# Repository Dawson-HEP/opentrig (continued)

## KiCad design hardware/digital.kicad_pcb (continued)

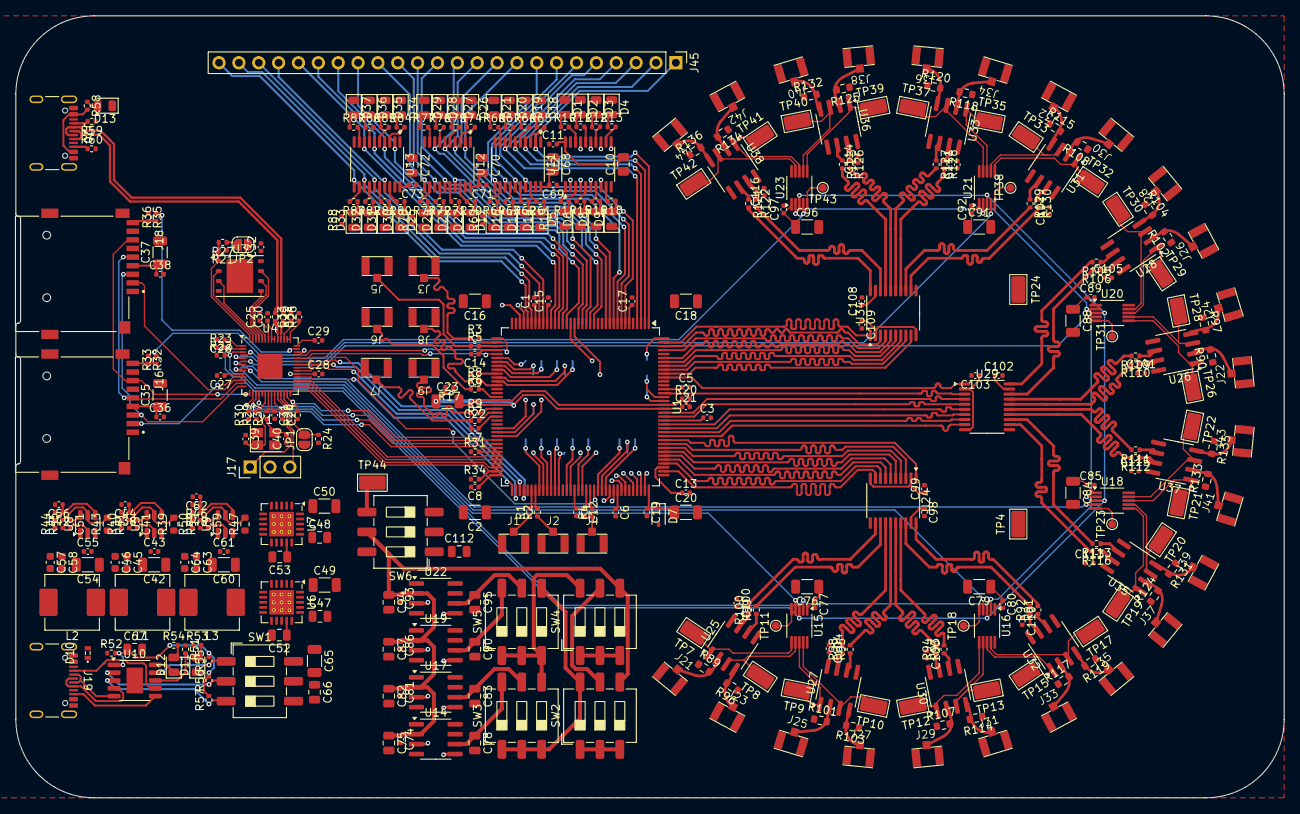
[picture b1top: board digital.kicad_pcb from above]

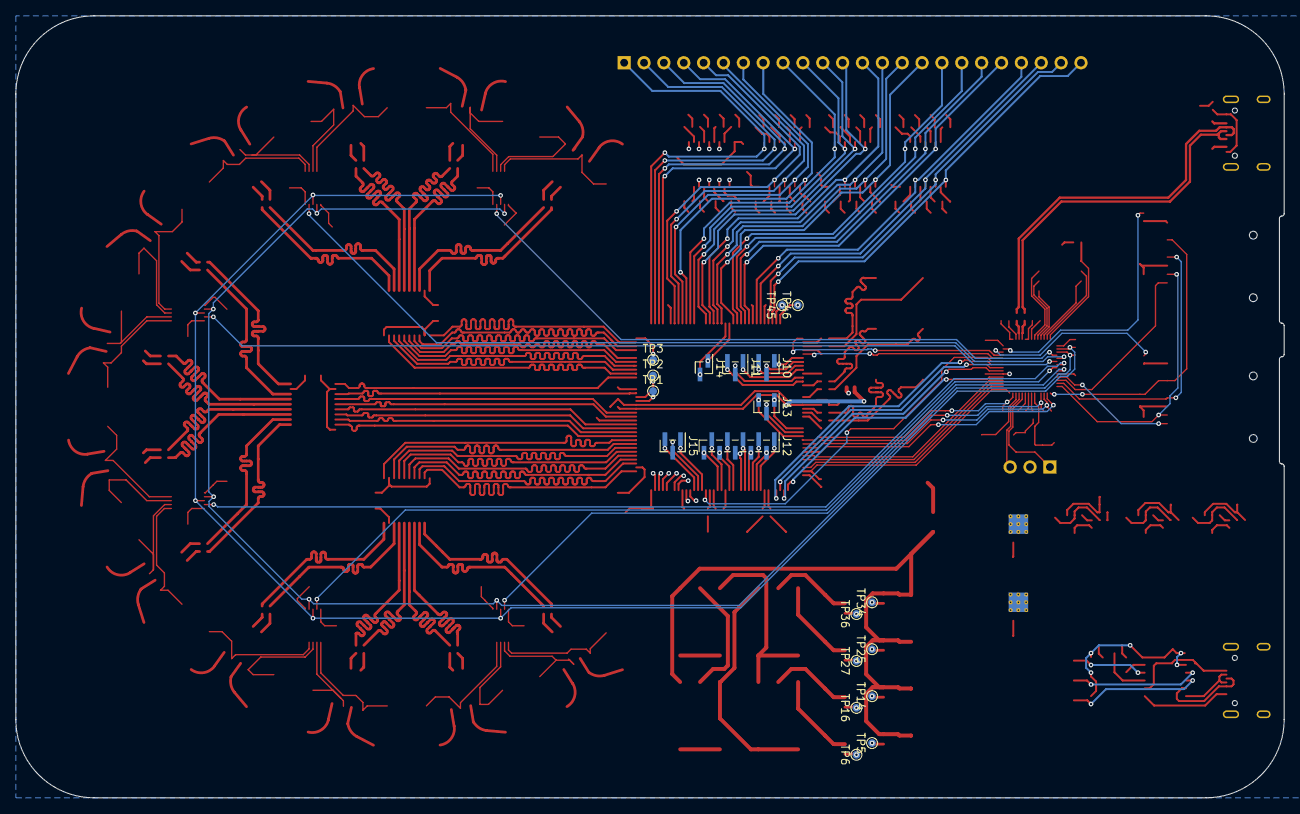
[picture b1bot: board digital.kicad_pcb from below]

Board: 4 copper layers, 162.2 x 100.0 mm, 429 parts (19 on the bottom side), 382 nets.

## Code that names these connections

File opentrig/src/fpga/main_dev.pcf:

set_io mcu_clk 37       # GPIO27
#set_io ext_clk 38               # External clock
        set_io ext_clk 44        # Internal clock from SIM PICO

set_io pll_clk 39
set_io pll_lock 41      # GPIO26

set_io t_zero_received 73

set_io spi_clk 70
set_io spi_cs 71
set_io spi_si 68
set_io spi_so 67

set_io veto_in 52
set_io trig_in 49
set_io trig_id 93
        #set_io veto_in 21
        #set_io trig_in 20
        #set_io trig_id 42

set_io trig_out 55
set_io veto_out 56

set_io global_reset 94
set_io mem_swap_interrupt 64


# mcu connections

set_io interrupt 63
set_io reset 64

# inputs
set_io c_input[0] 1
set_io c_input[1] 2
set_io c_input[2] 3
set_io c_input[3] 4
set_io c_input[4] 7
set_io c_input[5] 8
set_io c_input[6] 9
set_io c_input[7] 10
set_io c_input[8] 11
set_io c_input[9] 12
set_io c_input[10] 15
set_io c_input[11] 16
set_io c_input[12] 17
set_io c_input[13] 18
set_io c_input[14] 19
set_io c_input[15] 22
set_io c_input[16] 23
set_io c_input[17] 24
set_io c_input[18] 25
set_io c_input[19] 26
set_io c_input[20] 28
set_io c_input[21] 29
set_io c_input[22] 31
set_io c_input[23] 32

# led
set_io led[0] 98
set_io led[1] 99
set_io led[2] 101
set_io led[3] 102
set_io led[4] 104
set_io led[5] 105
set_io led[6] 106
set_io led[7] 107


# debug outputs
set_io aux_out[0] 80
set_io aux_out[1] 81
set_io aux_out[2] 82
set_io aux_out[3] 83
set_io aux_out[4] 84
set_io aux_out[5] 85
set_io aux_out[6] 87
set_io aux_out[7] 88
set_io aux_out[8] 90
set_io aux_out[9] 91

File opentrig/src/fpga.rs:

use defmt::*;
use embassy_rp::{
    gpio::{AnyPin, Input, Level, Output, Pull},
    pwm::{Config as PWMConfig, Pwm, SetDutyCycle},
    spi::{Async, Config as SPIConfig, Instance, Phase, Polarity, Spi},
};
use embassy_time::Timer;

pub struct DAQFpga<'a, T>
where
    T: Instance,
{
    spi: Spi<'a, T, Async>,

    cs: Output<'a>,
    creset: Output<'a>,
    cdone: Input<'a>,

    mcu_clk: Pwm<'a>,
    pll_lock: Input<'a>,

    reset_pin: Output<'a>,
    interrupt: Input<'a>,

    read_buffer: [u8; 16],
}

pub fn daq_fpga_spi_config() -> SPIConfig {
    let mut config = SPIConfig::default();
    config.frequency = 5_000_000;
    config.polarity = Polarity::IdleHigh;
    config.phase = Phase::CaptureOnSecondTransition;
    config
}

pub fn daq_fpga_clock_config() -> PWMConfig {
    let clock_freq_hz = embassy_rp::clocks::clk_sys_freq();
    let divider = 1u8;
    let period = (clock_freq_hz / (10_000_000 * divider as u32)) as u16 - 1;

    let mut c = PWMConfig::default();
    c.top = period;
    c.divider = divider.into();

    c
}

impl<'a, T> DAQFpga<'a, T>
where
    T: Instance,
{
    pub fn new(
        spi_bus: Spi<'a, T, Async>,

        cs: AnyPin,
        creset: AnyPin,
        cdone: AnyPin,

        mcu_clk: Pwm<'a>,
        pll_lock: AnyPin,

        reset_pin: AnyPin,
        interrupt: AnyPin,
    ) -> Self {
        Self {
            spi: spi_bus,

            cs: Output::new(cs, Level::Low),
            creset: Output::new(creset, Level::Low),
            cdone: Input::new(cdone, Pull::None),

            mcu_clk: mcu_clk,
            pll_lock: Input::new(pll_lock, Pull::Down),

            reset_pin: Output::new(reset_pin, Level::High),
            interrupt: Input::new(interrupt, Pull::None),

            read_buffer: [0u8; 16],
        }
    }

    pub async fn configure(&mut self, bitstream: &'static [u8]) -> Result<(), ()> {
        if self.cdone.is_low() {
            info!("config proceed");
        } else {
            info!("config err, cdone already high");
            return Err(());
        }

        self.creset.set_high();
        Timer::after_micros(1200).await;

        self.cs.set_high();
        self.spi.write(&[0]).await.map_err(|_| ())?;
        info!("ok 8 dummy");
        self.cs.set_low();

        info!("bitstream size: {}", bitstream.len());
        self.spi.write(bitstream).await.map_err(|_| ())?;
        info!("ok bitstream");
        self.cs.set_high();

        if self.cdone.is_high() {
            info!("last 49(56) cycles");
            self.spi.write(&[0xFFu8; 7]).await.map_err(|_| ())?;
            info!("last config 56 bits ok");
            info!("confirm config done");
        } else {
            warn!("cdone never high");
            return Err(());
        }

        Ok(())
    }

    pub async fn setup_clocks(&mut self) -> Result<(), ()> {
        self.mcu_clk.set_duty_cycle_percent(50).map_err(|_| ())?;

        while self.pll_lock.is_low() {
            warn!("pll not locked");
            Timer::after_millis(500).await;
        }
        info!("pll locked");

        Ok(())
    }

    pub fn reset(&mut self) -> Result<(), ()> {
        self.reset_pin.set_low();
        self.reset_pin.set_high();

        match self.interrupt.is_low() {
            true => {
                info!("reset success");
                Ok(())
            }
            false => {
                warn!("reset failed");
                Err(())
            }
        }
    }

    pub async fn await_sample(&mut self) {
        self.interrupt.wait_for_falling_edge().await;
    }

    pub fn last_sample_bytes(& self) -> &[u8; 16] {
        &self.read_buffer
    }

    // pub fn read_sample(&mut self) -> Result<DAQSample, ()> {
    pub fn read_sample(&mut self) {
        self.cs.set_low();
        self.spi
            .blocking_read(&mut self.read_buffer)
            .map_err(|_| ()).unwrap();
        self.cs.set_high();
    }
}

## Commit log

2025-06-30 Added the DAC/ADC array for analog conversion.
    Added an array of 6 quad-channels DAC with I2C interface to control the threshold voltage of a set of 12 dual channel ADCs. Loose, general wiring of FPGA and MCU present, detailed schematics in the w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
2025-07-02 Added SD card readers and USB-C for power in.
2025-07-03 generate pdfs
2025-07-09 Small aesthetic changes and small rework of power sheet.
2025-07-09 add power redundancy with OR-ing controller
2025-07-10 complete power
2025-07-11 reroute dac + comparators
2025-07-11 series resistors
2025-07-11 cleanup
2025-07-11 rewire
2025-07-11 annotate dip switches
2025-07-12 add notice
2025-07-12 cleanup kicad files
2025-07-12 refactor
2025-07-12 kicad + Rust exclusions
2025-07-12 Rust embassy boilerplate
2025-07-15 fpga .gitignore
2025-07-16 complete schematic wiring
2025-07-16 add kicad files
2025-07-16 add schematic pdf
2025-07-16 basic verilog bitstream programming
2025-07-17 remove kicad autosaves
2025-07-17 update power system + add LCSC part numbers
2025-07-17 apply manufacturing BOM
2025-07-18 route digital inputs
2025-07-18 route power
2025-07-18 route more
2025-07-18 route mcu
2025-07-19 wire until sipm power
2025-07-20 route
2025-07-20 route all signal
2025-07-20 add board edge
2025-07-20 finish routing
2025-07-20 add edges
2025-07-21 finish pcb
2025-07-21 drc check pass
2025-07-21 fabrication
2025-07-31 not working
2025-08-02 fix bitstream writing
2025-08-02 fix fpga synth target
2025-08-02 rudimentary communication
2025-08-02 add trig id pin
2025-08-03 basic testing suite
2025-08-03 working shifting out
2025-08-03 trigger id generation
2025-08-03 event pins encoding
2025-08-04 working input clk pll
2025-08-04 shift in trigger_id
2025-08-05 update to newer embassy
2025-08-05 read over trigger id
2025-08-05 cleanup trigger
2025-08-05 read clock counter
2025-08-05 trigger time
2025-08-05 reduce clock bit width to 48
2025-08-05 registering inputs
2025-08-05 remove data
2025-08-05 working veto
2025-08-05 veto simulation
2025-08-05 event management
2025-08-05 refactor fpga code
2025-08-07 dac writing
2025-08-07 tester
2025-08-07 remove dac
2025-08-08 internal trigger bit
2025-08-11 add watchdog + success in physical reading
2025-08-11 add trigger data
2025-08-14 Initial DacManager implementation (WARNING!) This module is NOT YET TESTED. Expect future changes and refrain from immediate usage if possible. Future functionality: Change vref mode, Change gain mod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
2025-08-19 Added write functions for all MCP registers.
2025-08-28 branch for_cli, hopefully. initial daqsample serialisation test
2025-08-29 incompatible differences between opentrig and usb_raw_bulk
2025-09-02 working version of multicore with usb_raw_bulk
2025-09-05 Complete MCP4728 manager for the DAQ.
2025-09-05 ~half of function inputs are made, with u8 documentation. beginning to connect inputs with core transfers properly
2025-09-06 functions calling from the CLI inputs completed
2025-09-08 inputs work fully properly and with info! messages for working or not working. inclusion of daq causes program to crash for some reason.
2025-09-08 working without daq
2025-09-08 added rusb_for_tests
2025-09-08 working with new DacManager stuff
2025-09-08 Cli code with command encoding. Needs to be reviewed and tested
2025-09-08 Fixed zip removing trailing arguments
2025-09-08 Fixed a bug introduced when taking excess args
2025-09-09 Added more thorough error mapping.
2025-09-09 Added info calls for easier debugging and control.
2025-09-09 all function inputs work with .await.unwrap()
2025-09-09 fix watchdog
2025-09-10 python cli
2025-09-10 opentrig
2025-09-10 rusb cli
2025-09-10 Last fix.
2025-09-14 Added rust CLI initial commit
2025-09-14 Added basic serial, readings packets from DAQ (to test)
2025-09-15 tons of stuff done
2025-09-15 Test
2025-09-15 Made readout work
2025-09-15 Added serial
2025-09-15 working version on pico! (only if computer/usb-connection is active, for the moment)
2025-09-15 Added no_serial_cli to git
2025-09-15 andy's location.py
2025-09-15 new main test
2025-09-15 main.bin for fpga
2025-09-15 remove old
2025-09-15 new cli
2025-09-16 change pcf for DESY
2025-09-16 encoding directly from fpga sent over should work
2025-09-16 simplify CLI buffering transfer
2025-09-16 Added MCP manager.
2025-09-16 Correct end and start byte
2025-09-16 chec end bit
2025-09-16 unworking minimal cli
2025-09-16 Added count events
2025-09-16 basic data reading
2025-09-16 data transfer works in current main, others for tests
2025-09-16 basic usb sending
2025-09-16 Fixed error
2025-09-16 basic filesaving
2025-09-16 remove debug statments
2025-09-16 Removed doubling for counting
2025-09-16 Renamed function
2025-09-16 64 size packet modified to 12
2025-09-16 all on core 0, 1 sample sent
2025-09-16 forgot the loop {}
2025-09-16 removed info! and println! statements
2025-09-16 frequency monitoring
2025-09-16 Added default MCP voltage setting to the minimal example.
2025-09-16 Fixed ldac pins.
2025-09-16 bomb everything
2025-09-16 increase arena to 4096
2025-09-17 IT WORKS (hopefully). pushing before breaking changes get made
2025-09-17 IT ALL WORKS!! (tested with set_all_voltages) (both pico code and CLI) (note: no feature for SD card as of yet)
2025-09-17 CLI no serial
2025-09-17 double latch length
2025-09-17 trig in cycles
2025-09-17 Revert "increase arena to 4096"
    This reverts commit f688646032f3647c0ed2615c806ef52622f33f4d.
2025-09-19 copied fpga.rs from minimal branch, not tested in this branch
2025-09-21 add forceful four channels
2025-11-08 add documentation & readme
2025-11-08 add links
2025-11-08 add license
2025-11-09 add picture of bare PCB
2025-11-09 add DESY picture
2025-11-09 add DESY TB info
2026-01-30 First version of the dual coincidence module. !Run only for tests!
2026-01-30 Fixed syntax errors
2026-02-03 Removed coincidence_trigger dependence on latch.v The coincidence_trigger module now has local latches. The input is now the genuine async input.
2026-02-08 Initial draft
2026-02-10 dev compilation target + pcf
2026-02-11 Initial fix for clock issues
2026-02-18 increase main pico task arena size to 4096
2026-02-18 use internal SIM PICO clock on PCF
2026-02-18 add input mask settings file, with TIMING & TRIGGER ERROR
2026-02-18 coincidence trigger
2026-02-18 adjustable PLL multiplication factor for reference clock
2026-02-18 add settings conditionals
2026-02-19 Working coincidence unoptimized
2026-02-19 add coincidence sampling window setting
2026-02-19 Added latching for variable coincidence window.
2026-02-19 add udev rules for USB CLI
2026-03-02 add udev rules for USB interfacing
2026-03-10 update trigger information
2026-03-27 Added the dev pinoout and commands for FPGA.
2026-03-27 Fixed issues in the justfile routing.
